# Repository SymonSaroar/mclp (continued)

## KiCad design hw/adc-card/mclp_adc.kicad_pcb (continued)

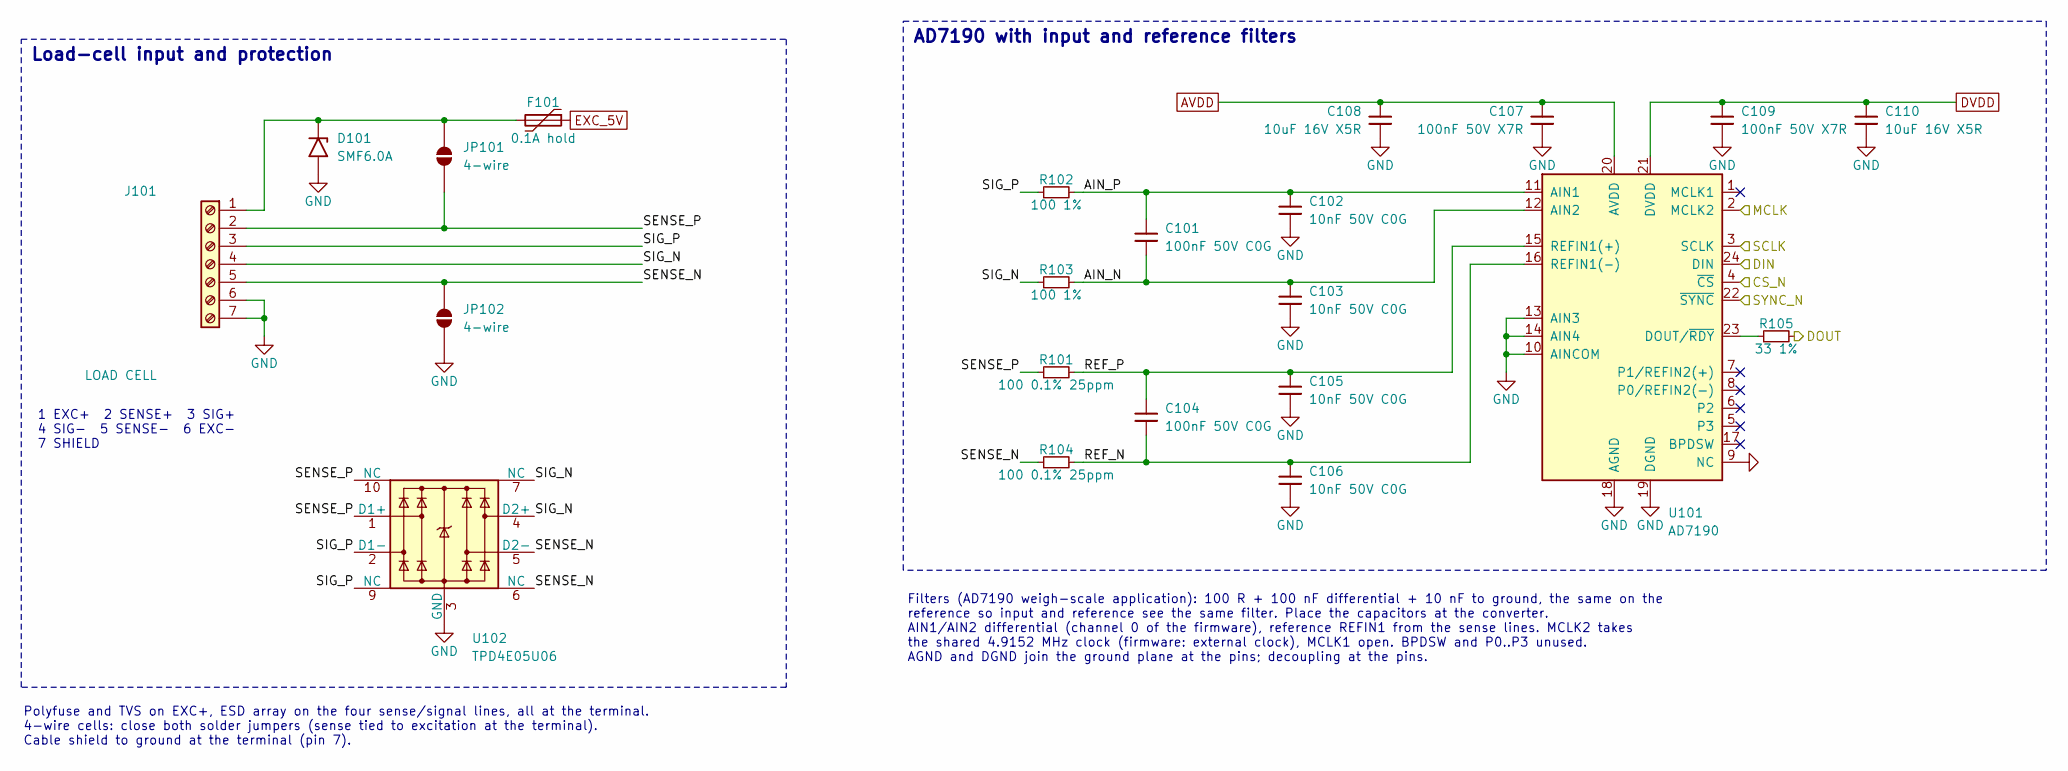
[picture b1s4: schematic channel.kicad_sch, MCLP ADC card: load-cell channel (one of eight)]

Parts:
C101, C104: 100nF 50V C0G; C_0805_2012Metric
C102, C103, C105, C106: 10nF 50V C0G; C_0603_1608Metric
C107, C109: 100nF 50V X7R; C_0603_1608Metric
C108, C110: 10uF 16V X5R; C_0805_2012Metric
D101: SMF6.0A; D_SMF; MPN Littelfuse SMF6.0A (unidirectional, 6 V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
F101: 0.1A hold; Fuse_0805_2012Metric; MPN Littelfuse 0805L010WR
J101: LOAD CELL; PhoenixContact_MC_1,5_7-G-3.5_1x07_P3.50mm_Horizontal; MPN Phoenix Contact MC 1,5/7-G-3,5 + plug M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
JP101, JP102: 4-wire; SolderJumper-2_P1.3mm_Open_RoundedPad1.0x1.5mm
R101, R104: 100 0.1% 25ppm; R_0603_1608Metric; MPN Panasonic ERA-3AEB101V
R102, R103: 100 1%; R_0603_1608Metric
R105: 33 1%; R_0603_1608Metric
U101: AD7190; TSSOP-24_4.4x7.8mm_P0.65mm; MPN ADI AD7190BRUZ
U102: TPD4E05U06; USON-10_2.5x1.0mm_P0.5mm; MPN TI TPD4E05U06DQAR

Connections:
/CH0/AIN_N: C101.2, C103.1, R103.2, U101.12 (AIN2)
/CH0/AIN_P: C101.1, C102.1, R102.2, U101.11 (AIN1)
/CH0/REF_N: C104.2, C106.1, R104.2, U101.16 (REFIN1(-))
/CH0/REF_P: C104.1, C105.1, R101.2, U101.15 (REFIN1(+))
/CH0/SENSE_N: J101.5, JP102.1 (A), R104.1, U102.5 (D2-), U102.6 (NC)
/CH0/SENSE_P: J101.2, JP101.1 (A), R101.1, U102.1 (D1+), U102.10 (NC)
/CH0/SIG_N: J101.4, R103.1, U102.4 (D2+), U102.7 (NC)
/CH0/SIG_P: J101.3, R102.1, U102.2 (D1-), U102.9 (NC)
AVDD: C107.1, C108.1, U101.20 (AVDD); also elsewhere on the board
CS_A_N: U101.4 (~CS); also elsewhere on the board
DIN_A: U101.24 (DIN); also elsewhere on the board
DOUT0: R105.2; also elsewhere on the board
DVDD: C109.1, C110.1, U101.21 (DVDD); also elsewhere on the board
EXC_5V: F101.1; also elsewhere on the board
GND: C102.2, C103.2, C105.2, C106.2, C107.2, C108.2, C109.2, C110.2, D101.2 (A2), J101.6, J101.7, JP102.2 (B), U101.9 (NC), U101.10 (AINCOM), U101.13 (AIN3), U101.14 (AIN4), U101.18 (AGND), U101.19 (DGND), U102.3 (GND), U102.8 (GND); also elsewhere on the board
MCLK0: U101.2 (MCLK2); also elsewhere on the board
unnamed: D101.1 (A1), F101.2, J101.1, JP101.2 (B)
unnamed: R105.1, U101.23 (DOUT/~RDY)
SCLK_A: U101.3 (SCLK); also elsewhere on the board
SYNC_A_N: U101.22 (~SYNC); also elsewhere on the board

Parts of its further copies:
C201, C204, C301, C304, C401, C404, C501, C504, C601, C604, C701, C704, C801, C804: 100nF 50V C0G; C_0805_2012Metric
C202, C203, C205, C206, C302, C303, C305, C306, C402, C403, C405, C406, C502, C503, C505, C506, C602, C603, C605, C606, C702, C703, C705, C706, C802, C803, C805, C806: 10nF 50V C0G; C_0603_1608Metric
C207, C209, C307, C309, C407, C409, C507, C509, C607, C609, C707, C709, C807, C809: 100nF 50V X7R; C_0603_1608Metric
C208, C210, C308, C310, C408, C410, C508, C510, C608, C610, C708, C710, C808, C810: 10uF 16V X5R; C_0805_2012Metric
D201, D301, D401, D501, D601, D701, D801: SMF6.0A; D_SMF; MPN Littelfuse SMF6.0A (unidirectional, 6 V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
F201, F301, F401, F501, F601, F701, F801: 0.1A hold; Fuse_0805_2012Metric; MPN Littelfuse 0805L010WR
J201, J301, J401, J501, J601, J701, J801: LOAD CELL; PhoenixContact_MC_1,5_7-G-3.5_1x07_P3.50mm_Horizontal; MPN Phoenix Contact MC 1,5/7-G-3,5 + plug M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
JP201, JP202, JP301, JP302, JP401, JP402, JP501, JP502, JP601, JP602, JP701, JP702, JP801, JP802: 4-wire; SolderJumper-2_P1.3mm_Open_RoundedPad1.0x1.5mm
R201, R204, R301, R304, R401, R404, R501, R504, R601, R604, R701, R704, R801, R804: 100 0.1% 25ppm; R_0603_1608Metric; MPN Panasonic ERA-3AEB101V
R202, R203, R302, R303, R402, R403, R502, R503, R602, R603, R702, R703, R802, R803: 100 1%; R_0603_1608Metric
R205, R305, R405, R505, R605, R705, R805: 33 1%; R_0603_1608Metric
U201, U301, U401, U501, U601, U701, U801: AD7190; TSSOP-24_4.4x7.8mm_P0.65mm; MPN ADI AD7190BRUZ
U202, U302, U402, U502, U602, U702, U802: TPD4E05U06; USON-10_2.5x1.0mm_P0.5mm; MPN TI TPD4E05U06DQAR

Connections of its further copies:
/CH1/AIN_N: C201.2, C203.1, R203.2, U201.12 (AIN2)
/CH1/AIN_P: C201.1, C202.1, R202.2, U201.11 (AIN1)
/CH1/REF_N: C204.2, C206.1, R204.2, U201.16 (REFIN1(-))
/CH1/REF_P: C204.1, C205.1, R201.2, U201.15 (REFIN1(+))
/CH1/SENSE_N: J201.5, JP202.1 (A), R204.1, U202.5 (D2-), U202.6 (NC)
/CH1/SENSE_P: J201.2, JP201.1 (A), R201.1, U202.1 (D1+), U202.10 (NC)
/CH1/SIG_N: J201.4, R203.1, U202.4 (D2+), U202.7 (NC)
/CH1/SIG_P: J201.3, R202.1, U202.2 (D1-), U202.9 (NC)
/CH2/AIN_N: C301.2, C303.1, R303.2, U301.12 (AIN2)
/CH2/AIN_P: C301.1, C302.1, R302.2, U301.11 (AIN1)
/CH2/REF_N: C304.2, C306.1, R304.2, U301.16 (REFIN1(-))
/CH2/REF_P: C304.1, C305.1, R301.2, U301.15 (REFIN1(+))
/CH2/SENSE_N: J301.5, JP302.1 (A), R304.1, U302.5 (D2-), U302.6 (NC)
/CH2/SENSE_P: J301.2, JP301.1 (A), R301.1, U302.1 (D1+), U302.10 (NC)
/CH2/SIG_N: J301.4, R303.1, U302.4 (D2+), U302.7 (NC)
/CH2/SIG_P: J301.3, R302.1, U302.2 (D1-), U302.9 (NC)
/CH3/AIN_N: C401.2, C403.1, R403.2, U401.12 (AIN2)
/CH3/AIN_P: C401.1, C402.1, R402.2, U401.11 (AIN1)
/CH3/REF_N: C404.2, C406.1, R404.2, U401.16 (REFIN1(-))
/CH3/REF_P: C404.1, C405.1, R401.2, U401.15 (REFIN1(+))
/CH3/SENSE_N: J401.5, JP402.1 (A), R404.1, U402.5 (D2-), U402.6 (NC)
/CH3/SENSE_P: J401.2, JP401.1 (A), R401.1, U402.1 (D1+), U402.10 (NC)
/CH3/SIG_N: J401.4, R403.1, U402.4 (D2+), U402.7 (NC)
/CH3/SIG_P: J401.3, R402.1, U402.2 (D1-), U402.9 (NC)
/CH4/AIN_N: C501.2, C503.1, R503.2, U501.12 (AIN2)
/CH4/AIN_P: C501.1, C502.1, R502.2, U501.11 (AIN1)
/CH4/REF_N: C504.2, C506.1, R504.2, U501.16 (REFIN1(-))
/CH4/REF_P: C504.1, C505.1, R501.2, U501.15 (REFIN1(+))
/CH4/SENSE_N: J501.5, JP502.1 (A), R504.1, U502.5 (D2-), U502.6 (NC)
/CH4/SENSE_P: J501.2, JP501.1 (A), R501.1, U502.1 (D1+), U502.10 (NC)
/CH4/SIG_N: J501.4, R503.1, U502.4 (D2+), U502.7 (NC)
/CH4/SIG_P: J501.3, R502.1, U502.2 (D1-), U502.9 (NC)
/CH5/AIN_N: C601.2, C603.1, R603.2, U601.12 (AIN2)
/CH5/AIN_P: C601.1, C602.1, R602.2, U601.11 (AIN1)
/CH5/REF_N: C604.2, C606.1, R604.2, U601.16 (REFIN1(-))
/CH5/REF_P: C604.1, C605.1, R601.2, U601.15 (REFIN1(+))
/CH5/SENSE_N: J601.5, JP602.1 (A), R604.1, U602.5 (D2-), U602.6 (NC)
/CH5/SENSE_P: J601.2, JP601.1 (A), R601.1, U602.1 (D1+), U602.10 (NC)
/CH5/SIG_N: J601.4, R603.1, U602.4 (D2+), U602.7 (NC)
/CH5/SIG_P: J601.3, R602.1, U602.2 (D1-), U602.9 (NC)
/CH6/AIN_N: C701.2, C703.1, R703.2, U701.12 (AIN2)
/CH6/AIN_P: C701.1, C702.1, R702.2, U701.11 (AIN1)
/CH6/REF_N: C704.2, C706.1, R704.2, U701.16 (REFIN1(-))
/CH6/REF_P: C704.1, C705.1, R701.2, U701.15 (REFIN1(+))
/CH6/SENSE_N: J701.5, JP702.1 (A), R704.1, U702.5 (D2-), U702.6 (NC)
/CH6/SENSE_P: J701.2, JP701.1 (A), R701.1, U702.1 (D1+), U702.10 (NC)
/CH6/SIG_N: J701.4, R703.1, U702.4 (D2+), U702.7 (NC)
/CH6/SIG_P: J701.3, R702.1, U702.2 (D1-), U702.9 (NC)
/CH7/AIN_N: C801.2, C803.1, R803.2, U801.12 (AIN2)
/CH7/AIN_P: C801.1, C802.1, R802.2, U801.11 (AIN1)
/CH7/REF_N: C804.2, C806.1, R804.2, U801.16 (REFIN1(-))
/CH7/REF_P: C804.1, C805.1, R801.2, U801.15 (REFIN1(+))
/CH7/SENSE_N: J801.5, JP802.1 (A), R804.1, U802.5 (D2-), U802.6 (NC)
/CH7/SENSE_P: J801.2, JP801.1 (A), R801.1, U802.1 (D1+), U802.10 (NC)
/CH7/SIG_N: J801.4, R803.1, U802.4 (D2+), U802.7 (NC)
/CH7/SIG_P: J801.3, R802.1, U802.2 (D1-), U802.9 (NC)
AVDD: C207.1, C208.1, C307.1, C308.1, C407.1, C408.1, C507.1, C508.1, C607.1, C608.1, C707.1, C708.1, C807.1, C808.1, U201.20 (AVDD), U301.20 (AVDD), U401.20 (AVDD), U501.20 (AVDD), U601.20 (AVDD), U701.20 (AVDD), U801.20 (AVDD); also elsewhere on the board
CS_A_N: U201.4 (~CS), U301.4 (~CS), U401.4 (~CS); also elsewhere on the board
CS_B_N: U501.4 (~CS), U601.4 (~CS), U701.4 (~CS), U801.4 (~CS); also elsewhere on the board
DIN_A: U201.24 (DIN), U301.24 (DIN), U401.24 (DIN); also elsewhere on the board
DIN_B: U501.24 (DIN), U601.24 (DIN), U701.24 (DIN), U801.24 (DIN); also elsewhere on the board
DOUT1: R205.2; also elsewhere on the board
DOUT2: R305.2; also elsewhere on the board
DOUT3: R405.2; also elsewhere on the board
DOUT4: R505.2; also elsewhere on the board
DOUT5: R605.2; also elsewhere on the board
DOUT6: R705.2; also elsewhere on the board
DOUT7: R805.2; also elsewhere on the board
DVDD: C209.1, C210.1, C309.1, C310.1, C409.1, C410.1, C509.1, C510.1, C609.1, C610.1, C709.1, C710.1, C809.1, C810.1, U201.21 (DVDD), U301.21 (DVDD), U401.21 (DVDD), U501.21 (DVDD), U601.21 (DVDD), U701.21 (DVDD), U801.21 (DVDD); also elsewhere on the board
EXC_5V: F201.1, F301.1, F401.1, F501.1, F601.1, F701.1, F801.1; also elsewhere on the board
GND: C202.2, C203.2, C205.2, C206.2, C207.2, C208.2, C209.2, C210.2, C302.2, C303.2, C305.2, C306.2, C307.2, C308.2, C309.2, C310.2, C402.2, C403.2, C405.2, C406.2, C407.2, C408.2, C409.2, C410.2, C502.2, C503.2, C505.2, C506.2, C507.2, C508.2, C509.2, C510.2, C602.2, C603.2, C605.2, C606.2, C607.2, C608.2, C609.2, C610.2, C702.2, C703.2, C705.2, C706.2, C707.2, C708.2, C709.2, C710.2, C802.2, C803.2, C805.2, C806.2, C807.2, C808.2, C809.2, C810.2, D201.2 (A2), D301.2 (A2), D401.2 (A2), D501.2 (A2), D601.2 (A2), D701.2 (A2), D801.2 (A2), J201.6, J201.7, J301.6, J301.7, J401.6, J401.7, J501.6, J501.7, J601.6, J601.7, J701.6, J701.7, J801.6, J801.7, JP202.2 (B), JP302.2 (B), JP402.2 (B), JP502.2 (B), JP602.2 (B), JP702.2 (B), JP802.2 (B), U201.9 (NC), U201.10 (AINCOM), U201.13 (AIN3), U201.14 (AIN4), U201.18 (AGND), U201.19 (DGND), U202.3 (GND), U202.8 (GND), U301.9 (NC), U301.10 (AINCOM), U301.13 (AIN3), U301.14 (AIN4), U301.18 (AGND), U301.19 (DGND), U302.3 (GND), U302.8 (GND), U401.9 (NC), U401.10 (AINCOM), U401.13 (AIN3), U401.14 (AIN4), U401.18 (AGND), U401.19 (DGND), U402.3 (GND), U402.8 (GND), U501.9 (NC), U501.10 (AINCOM), U501.13 (AIN3), U501.14 (AIN4), U501.18 (AGND), U501.19 (DGND), U502.3 (GND), U502.8 (GND), U601.9 (NC), U601.10 (AINCOM), U601.13 (AIN3), U601.14 (AIN4), U601.18 (AGND), U601.19 (DGND), U602.3 (GND), U602.8 (GND), U701.9 (NC), U701.10 (AINCOM), U701.13 (AIN3), U701.14 (AIN4), U701.18 (AGND), U701.19 (DGND), U702.3 (GND), U702.8 (GND), U801.9 (NC), U801.10 (AINCOM), U801.13 (AIN3), U801.14 (AIN4), U801.18 (AGND), U801.19 (DGND), U802.3 (GND), U802.8 (GND); also elsewhere on the board
MCLK1: U201.2 (MCLK2); also elsewhere on the board
MCLK2: U301.2 (MCLK2); also elsewhere on the board
MCLK3: U401.2 (MCLK2); also elsewhere on the board
MCLK4: U501.2 (MCLK2); also elsewhere on the board
MCLK5: U601.2 (MCLK2); also elsewhere on the board
MCLK6: U701.2 (MCLK2); also elsewhere on the board
MCLK7: U801.2 (MCLK2); also elsewhere on the board
unnamed: D201.1 (A1), F201.2, J201.1, JP201.2 (B)
unnamed: D301.1 (A1), F301.2, J301.1, JP301.2 (B)
unnamed: D401.1 (A1), F401.2, J401.1, JP401.2 (B)
unnamed: D501.1 (A1), F501.2, J501.1, JP501.2 (B)
unnamed: D601.1 (A1), F601.2, J601.1, JP601.2 (B)
unnamed: D701.1 (A1), F701.2, J701.1, JP701.2 (B)
unnamed: D801.1 (A1), F801.2, J801.1, JP801.2 (B)
unnamed: R205.1, U201.23 (DOUT/~RDY)
unnamed: R305.1, U301.23 (DOUT/~RDY)
unnamed: R405.1, U401.23 (DOUT/~RDY)
unnamed: R505.1, U501.23 (DOUT/~RDY)
unnamed: R605.1, U601.23 (DOUT/~RDY)
unnamed: R705.1, U701.23 (DOUT/~RDY)
unnamed: R805.1, U801.23 (DOUT/~RDY)
SCLK_A: U201.3 (SCLK), U301.3 (SCLK), U401.3 (SCLK); also elsewhere on the board
SCLK_B: U501.3 (SCLK), U601.3 (SCLK), U701.3 (SCLK), U801.3 (SCLK); also elsewhere on the board
SYNC_A_N: U201.22 (~SYNC), U301.22 (~SYNC), U401.22 (~SYNC); also elsewhere on the board
SYNC_B_N: U501.22 (~SYNC), U601.22 (~SYNC), U701.22 (~SYNC), U801.22 (~SYNC); also elsewhere on the board

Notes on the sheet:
1 EXC+ 2 SENSE+ 3 SIG+ 4 SIG- 5 SENSE- 6 EXC- 7 SHIELD
Load-cell input and protection
Polyfuse and TVS on EXC+, ESD array on the four sense/signal lines, all at the terminal. 4-wire cells: close both solder jumpers (sense tied to excitation at the terminal). Cable shield to ground at the terminal (pin 7).
AD7190 with input and reference filters
Filters (AD7190 weigh-scale application): 100 R + 100 nF differential + 10 nF to ground, the same on the reference so input and reference see the same filter. Place the capacitors at the converter. AIN1/AIN2 differential (channel 0 of the firmware), reference REFIN1 from the sense lines. MCLK2 take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

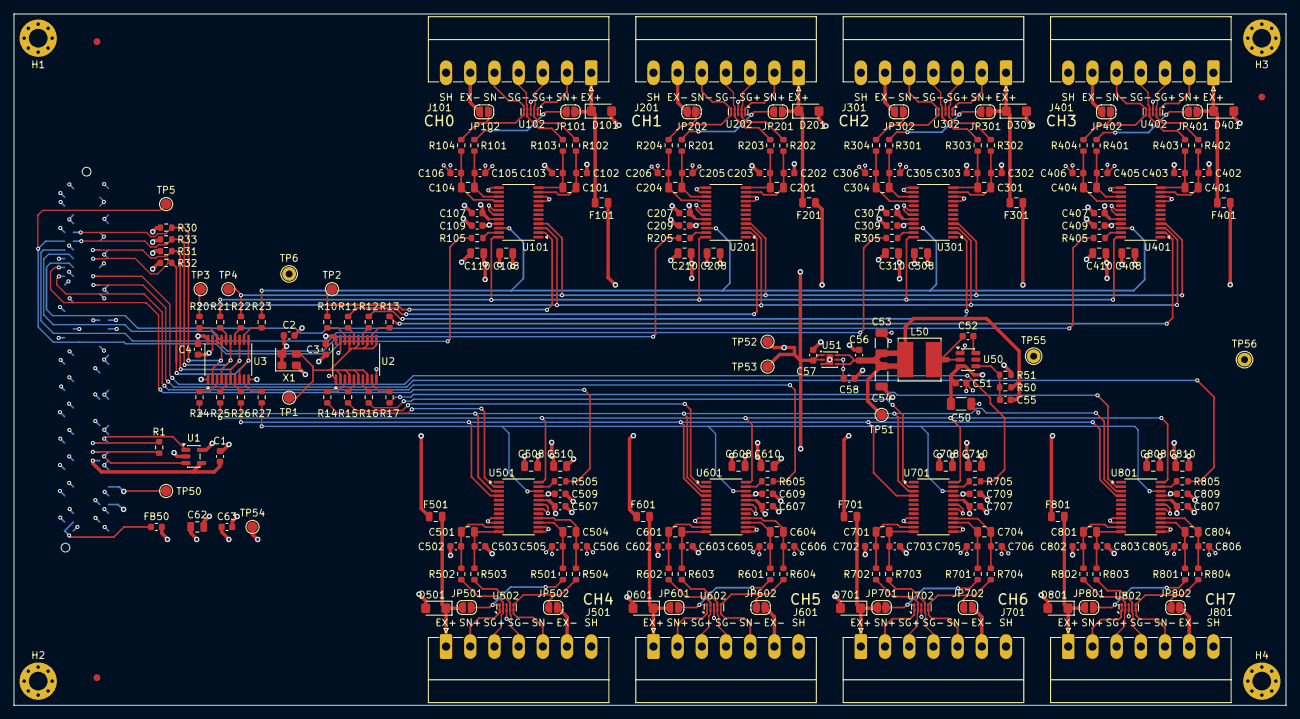
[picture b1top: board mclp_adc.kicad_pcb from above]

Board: 4 copper layers, 184.0 x 100.0 mm, 244 parts (1 on the bottom side), 141 nets.

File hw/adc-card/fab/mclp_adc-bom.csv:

"Qty","Value","Footprint","MPN","References"
"23","100nF 50V X7R","Capacitor_SMD:C_0603_1608Metric","","C1,C2,C3,C4,C51,C52,C63,C107,C109,C207,C209,C307,C309,C407,C409,C507,C509,C607,C609,C707,C709,C807,C809"
"1","10uF 25V X7R","Capacitor_SMD:C_1206_3216Metric","","C50"
"2","22uF 16V X7R","Capacitor_SMD:C_1206_3216Metric","","C53,C54"
"1","75pF 50V C0G","Capacitor_SMD:C_0603_1608Metric","","C55"
"2","2.2uF 16V X7R","Capacitor_SMD:C_0603_1608Metric","","C56,C57"
"1","1nF 50V C0G","Capacitor_SMD:C_0603_1608Metric","","C58"
"17","10uF 16V X5R","Capacitor_SMD:C_0805_2012Metric","","C62,C108,C110,C208,C210,C308,C310,C408,C410,C508,C510,C608,C610,C708,C710,C808,C810"
"16","100nF 50V C0G","Capacitor_SMD:C_0805_2012Metric","","C101,C104,C201,C204,C301,C304,C401,C404,C501,C504,C601,C604,C701,C704,C801,C804"
"32","10nF 50V C0G","Capacitor_SMD:C_0603_1608Metric","","C102,C103,C105,C106,C202,C203,C205,C206,C302,C303,C305,C306,C402,C403,C405,C406,C502,C503,C505,C506,C602,C603,C605,C606,C702,C703,C705,C706,C802,C803,C805,C806"
"8","SMF6.0A","Diode_SMD:D_SMF","Littelfuse SMF6.0A (unidirectional, 6 V standoff)","D101,D201,D301,D401,D501,D601,D701,D801"
"8","0.1A hold","Fuse:Fuse_0805_2012Metric","Littelfuse 0805L010WR","F101,F201,F301,F401,F501,F601,F701,F801"
"1","220R@100MHz","Inductor_SMD:L_0603_1608Metric","Murata BLM18PG221SN1D","FB50"
"1","ASP-134604-01","Connector_Samtec:Samtec_FMC_ASP-134604-01_4x40_Vertical","Samtec ASP-134604-01 (check gender and stack height against the ZC702 J3)","J1"
"8","LOAD CELL","Connector_Phoenix_MC:PhoenixContact_MC_1,5_7-G-3.5_1x07_P3.50mm_Horizontal","Phoenix Contact MC 1,5/7-G-3,5 + plug MC 1,5/7-ST-3,5","J101,J201,J301,J401,J501,J601,J701,J801"
"1","22uH","Inductor_SMD:L_Bourns_SRN6045TA","Bourns SRN6045TA-220M (22 uH, Isat >= 1 A, shielded)","L50"
"1","0","Resistor_SMD:R_0603_1608Metric","","R1"
"24","33 1%","Resistor_SMD:R_0603_1608Metric","","R10,R11,R12,R13,R14,R15,R16,R17,R20,R21,R22,R23,R24,R25,R26,R27,R105,R205,R305,R405,R505,R605,R705,R805"
"4","10k 1%","Resistor_SMD:R_0603_1608Metric","","R30,R31,R32,R33"
"1","100k 1%","Resistor_SMD:R_0603_1608Metric","","R50"
"1","11.0k 1%","Resistor_SMD:R_0603_1608Metric","","R51"
"16","100 0.1% 25ppm","Resistor_SMD:R_0603_1608Metric","Panasonic ERA-3AEB101V","R101,R104,R201,R204,R301,R304,R401,R404,R501,R504,R601,R604,R701,R704,R801,R804"
"16","100 1%","Resistor_SMD:R_0603_1608Metric","","R102,R103,R202,R203,R302,R303,R402,R403,R502,R503,R602,R603,R702,R703,R802,R803"
"1","24AA02","Package_TO_SOT_SMD:SOT-23-5","Microchip 24AA02T-I/OT","U1"
"2","74AHC244","Package_SO:TSSOP-20_4.4x6.5mm_P0.65mm","TI SN74AHC244PWR","U2,U3"
"1","TPS54202DDC","Package_TO_SOT_SMD:SOT-23-6","TI TPS54202DDCR","U50"
"1","ADP7118ACPZN5.0","Package_CSP:LFCSP-6-1EP_2x2mm_P0.65mm_EP1x1.6mm","ADI ADP7118ACPZN5.0-R7 (fixed 5.0 V; confirm the ordering code)","U51"
"8","AD7190","Package_SO:TSSOP-24_4.4x7.8mm_P0.65mm","ADI AD7190BRUZ","U101,U201,U301,U401,U501,U601,U701,U801"
"8","TPD4E05U06","Package_SON:USON-10_2.5x1.0mm_P0.5mm","TI TPD4E05U06DQAR","U102,U202,U302,U402,U502,U602,U702,U802"
"1","4.9152MHz","Oscillator:Oscillator_SMD_Abracon_ASE-4Pin_3.2x2.5mm","Abracon ASE series, 4.9152 MHz, 3.3 V CMOS","X1"
